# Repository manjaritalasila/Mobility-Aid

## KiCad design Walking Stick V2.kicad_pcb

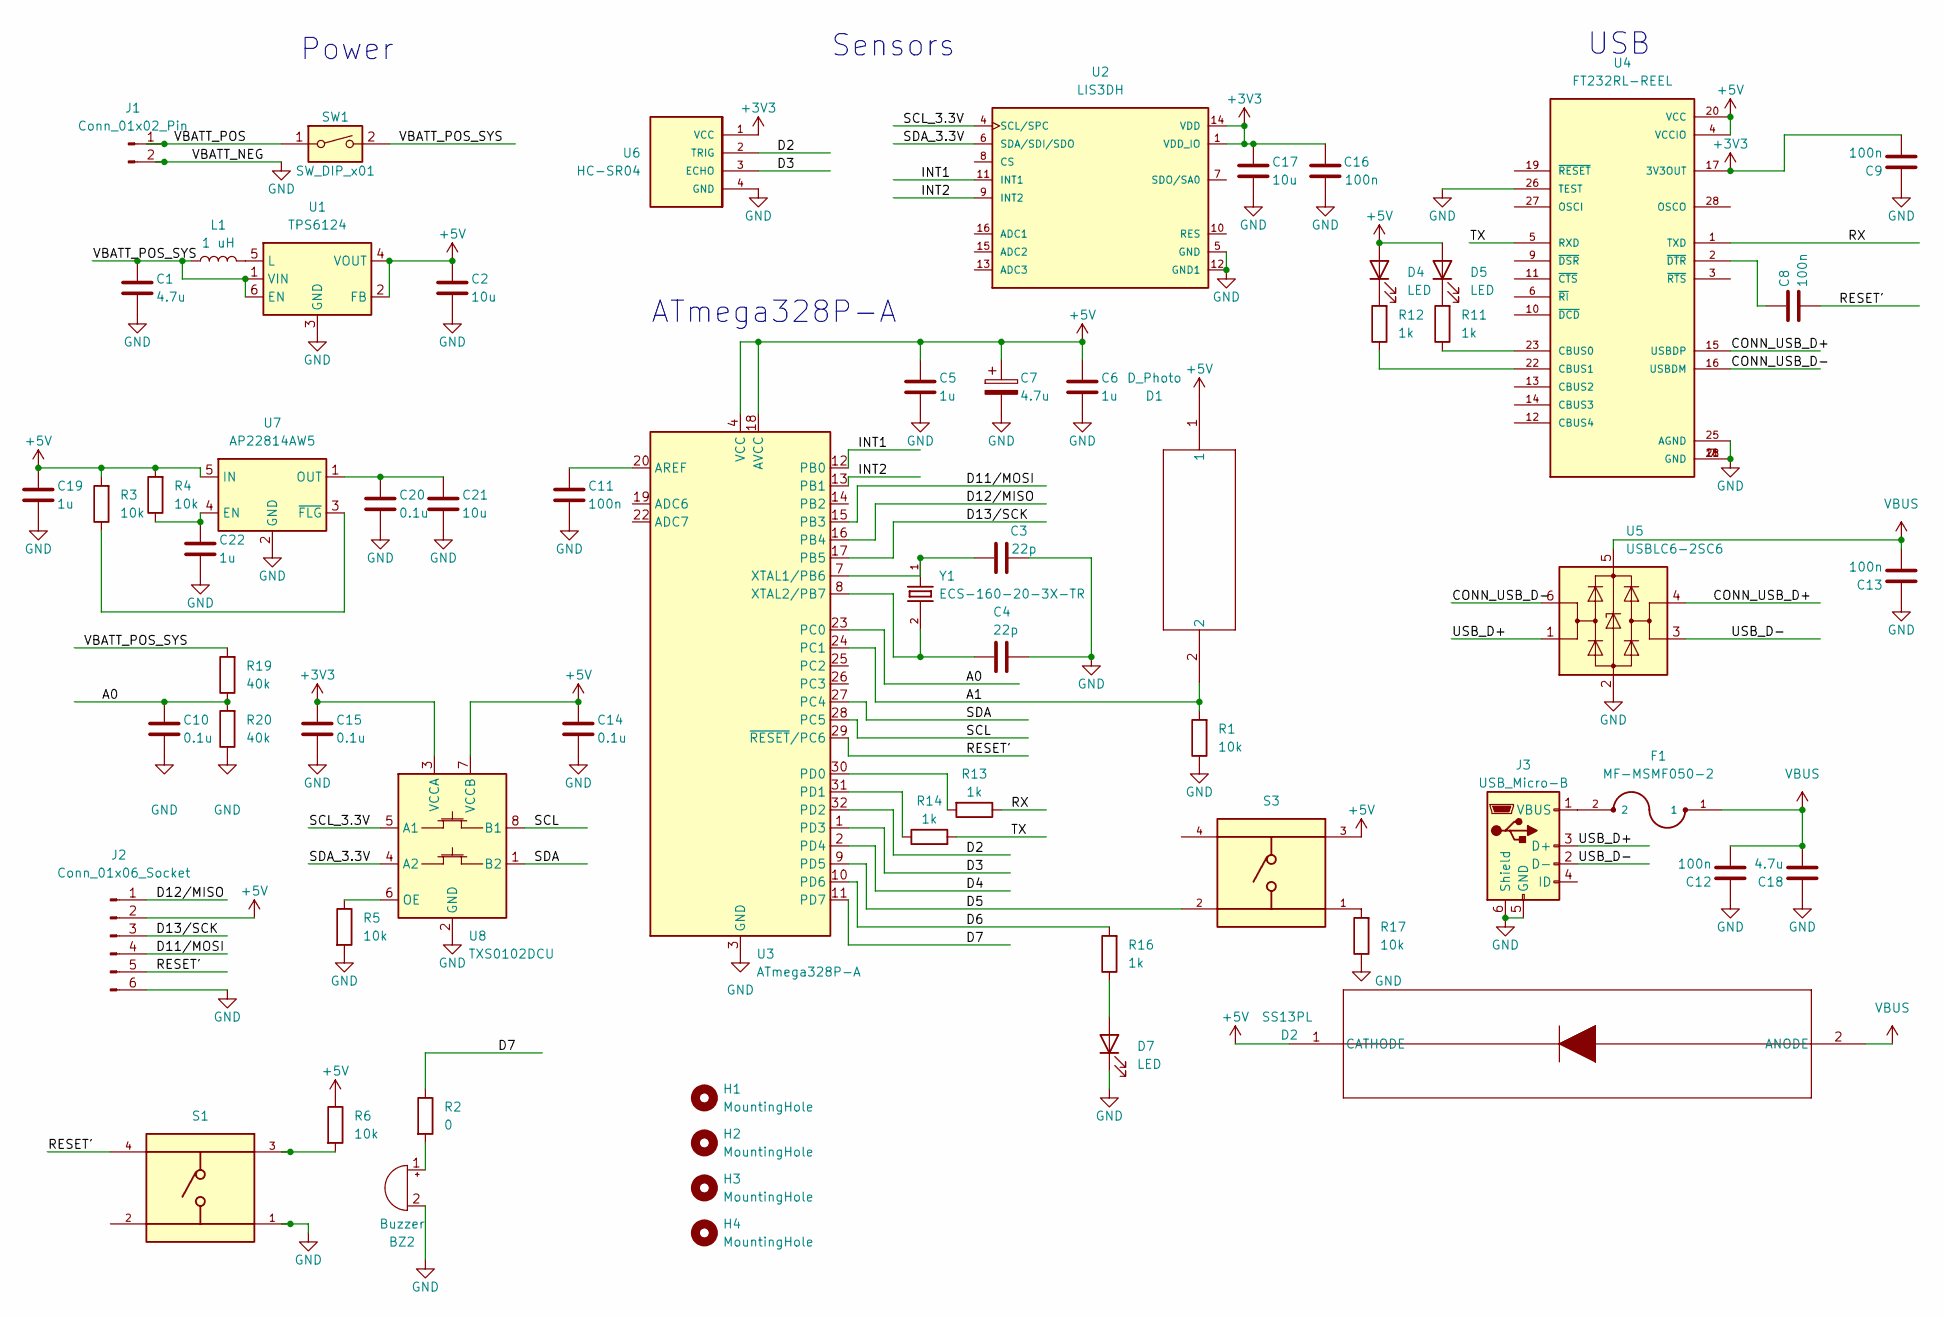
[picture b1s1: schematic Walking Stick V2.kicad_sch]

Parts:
BZ2: Buzzer; Buzzer_12x9.5RM7.6
C1, C7, C18: 4.7u; C_0603_1608Metric
C2, C17, C21: 10u; C_0603_1608Metric
C3, C4: 22p; C_0603_1608Metric
C5, C6, C19, C22: 1u; C_0603_1608Metric
C8, C9, C11, C12, C13, C16: 100n; C_0603_1608Metric
C10, C14, C15, C20: 0.1u; C_0603_1608Metric
D1: D_Photo; TO_NSL_19M_ADP
D2: SS13PL; DIODE_SS1P3L-M3&slash_84A_VIS-L
D4, D5, D7: LED; LED_0402_1005Metric
F1: MF-MSMF050-2; FUSM4632X85
H1, H2, H3, H4: MountingHole; MountingHole_2.1mm
J1: Conn_01x02_Pin; AMASS_XT30UPB-M_1x02_P5.0mm_Vertical
J2: Conn_01x06_Socket; PinHeader_1x06_P2.54mm_Vertical
J3: USB_Micro-B; USB_Micro-B_Molex-105133-0031
L1: 1 uH; L_0603_1608Metric_Pad1.05x0.95mm_HandSolder
R1, R3, R4, R5, R6, R17: 10k; R_0603_1608Metric
R2: 0; R_0603_1608Metric
R11, R12, R13, R14, R16: 1k; R_0603_1608Metric
R19, R20: 40k; R_0603_1608Metric
S1, S3: SW_TS02-66-60-BK-160-LCR-D; PART-NUMBER 471005264152
SW1: SW_DIP_x01; SW_DIP_SPSTx01_Slide_6.7x4.1mm_W6.73mm_P2.54mm_LowProfile_J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
U1: TPS6124; WSON-6-1EP_2x2mm_P0.65mm_EP1x1.6mm
U2: LIS3DH; PQFN50P300X300X100-16N
U3: ATmega328P-A; TQFP-32_7x7mm_P0.8mm
U4: FT232RL-REEL; SOP65P780X200-28N
U5: USBLC6-2SC6; SOT-23-6
U6: HC-SR04; XCVR_HC-SR04
U7: AP22814AW5; SOT-23-5
U8: TXS0102DCU; VSSOP-8_2.3x2mm_P0.5mm
Y1: ECS-160-20-3X-TR; XTAL_ECS-160-20-3X-TR; PARTREV 2017

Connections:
+3V3: C9.2, C15.1, C16.2, C17.1, U2.1 (VDD_IO), U2.14 (VDD), U4.17 (3V3OUT), U6.1 (VCC), U8.3 (VCCA); also elsewhere on the board
+5V: C2.1, C5.1, C6.1, C7.1, C14.1, C19.1, D1.1, D2.1 (CATHODE), D4.2 (A), D5.2 (A), J2.2, R3.2, R4.2, R6.1, S3.3, U1.2 (FB), U1.4 (VOUT), U3.4 (VCC), U3.6 (VCC), U3.18 (AVCC), U4.4 (VCCIO), U4.20 (VCC), U7.5 (IN), U8.7 (VCCB); also elsewhere on the board
/A0: C10.1, R19.1, R20.2, U3.23 (PC0)
/A1: D1.2, R1.2, U3.24 (PC1)
/CONN_USB_D+: U4.15 (USBDP), U5.4 (I/O2)
/CONN_USB_D-: U4.16 (USBDM), U5.6 (I/O1)
/D2: U3.32 (PD2), U6.2 (TRIG)
/D3: U3.1 (PD3), U6.3 (ECHO)
/D4: U3.2 (PD4)
/D5: S3.2, U3.9 (PD5)
/D6: R16.2, U3.10 (PD6)
/D7: R2.1, U3.11 (PD7)
/D11/MOSI: J2.4, U3.15 (PB3)
/D12/MISO: J2.1, U3.16 (PB4)
/D13/SCK: J2.3, U3.17 (PB5)
/INT1: U2.11 (INT1), U3.12 (PB0)
/INT2: U2.9 (INT2), U3.13 (PB1)
/RESET': C8.2, J2.5, S1.4, U3.29 (~RESET/PC6)
/RX: R13.1, U4.1 (TXD)
/SCL: U3.28 (PC5), U8.8 (B1)
/SCL_3.3V: U2.4 (SCL/SPC), U8.5 (A1)
/SDA: U3.27 (PC4), U8.1 (B2)
/SDA_3.3V: U2.6 (SDA/SDI/SDO), U8.4 (A2)
/TX: R14.2, U4.5 (RXD)
/USB_D+: J3.3 (D+), U5.1 (I/O1)
/USB_D-: J3.2 (D-), U5.3 (I/O2)
/VBATT_POS: J1.1, SW1.1
/VBATT_POS_SYS: C1.1, L1.1, R19.2, SW1.2, U1.1 (VIN), U1.6 (EN)
GND: BZ2.2 (+), C1.2, C2.2, C3.2, C4.1, C5.2, C6.2, C7.2, C9.1, C10.2, C11.2, C12.1, C13.1, C14.2, C15.2, C16.1, C17.2, C18.1, C19.2, C20.2, C21.2, C22.2, D7.1 (K), J1.2, J2.6, J3.5 (GND), J3.6 (Shield), R1.1, R5.2, R17.1, R20.1, S1.1, U1.3 (GND), U2.5 (GND), U2.12 (GND1), U3.3 (GND), U3.5 (GND), U3.21 (GND), U4.7 (GND), U4.18 (GND), U4.21 (GND), U4.25 (AGND), U4.26 (TEST), U5.2 (GND), U6.4 (GND), U7.2 (GND), U8.2 (GND); also elsewhere on the board
unnamed: BZ2.1 (-), R2.2
unnamed: D4.1 (K), R12.2
unnamed: D5.1 (K), R11.2
unnamed: D7.2 (A), R16.1
unnamed: F1.2, J3.1 (VBUS)
unnamed: R6.2, S1.3
unnamed: R17.2, S3.1
unnamed: L1.2, U1.5 (L)
unnamed: C11.1, U3.20 (AREF)
unnamed: R13.2, U3.30 (PD0)
unnamed: R14.1, U3.31 (PD1)
unnamed: C3.1, U3.7 (XTAL1/PB6), Y1.1
unnamed: C4.2, U3.8 (XTAL2/PB7), Y1.2
unnamed: R11.1, U4.23 (CBUS0)
unnamed: R12.1, U4.22 (CBUS1)
unnamed: C8.1, U4.2 (~DTR)
unnamed: C22.1, R4.1, U7.4 (EN)
unnamed: C20.1, C21.1, U7.1 (OUT)
unnamed: R3.1, U7.3 (~FLG)
unnamed: R5.1, U8.6 (OE)
VBUS: C12.2, C13.2, C18.2, D2.2 (ANODE), F1.1, U5.5 (VBUS)

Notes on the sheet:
ATmega328P-A
Sensors
Power
USB

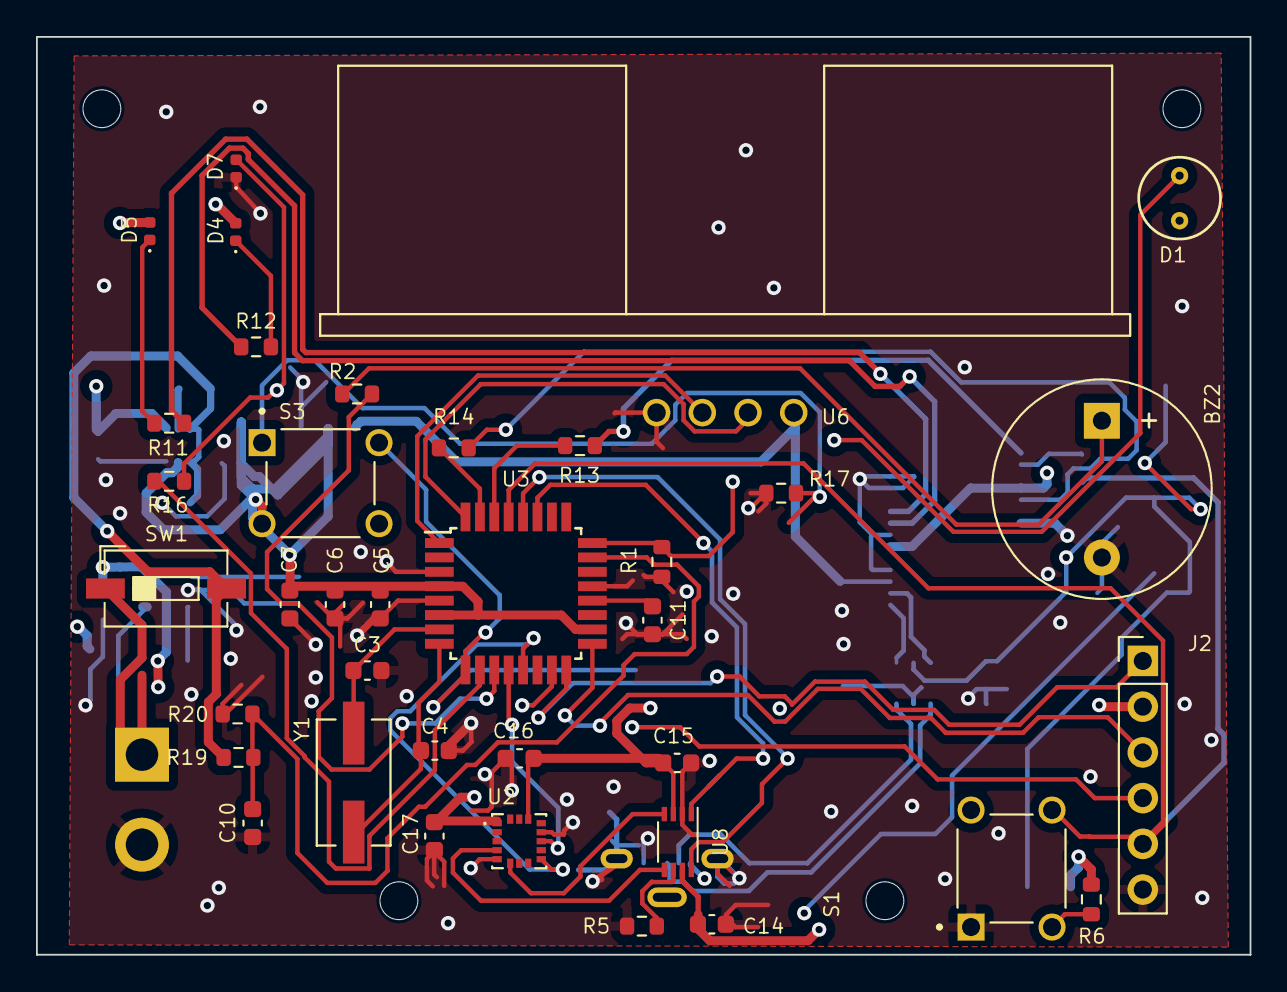
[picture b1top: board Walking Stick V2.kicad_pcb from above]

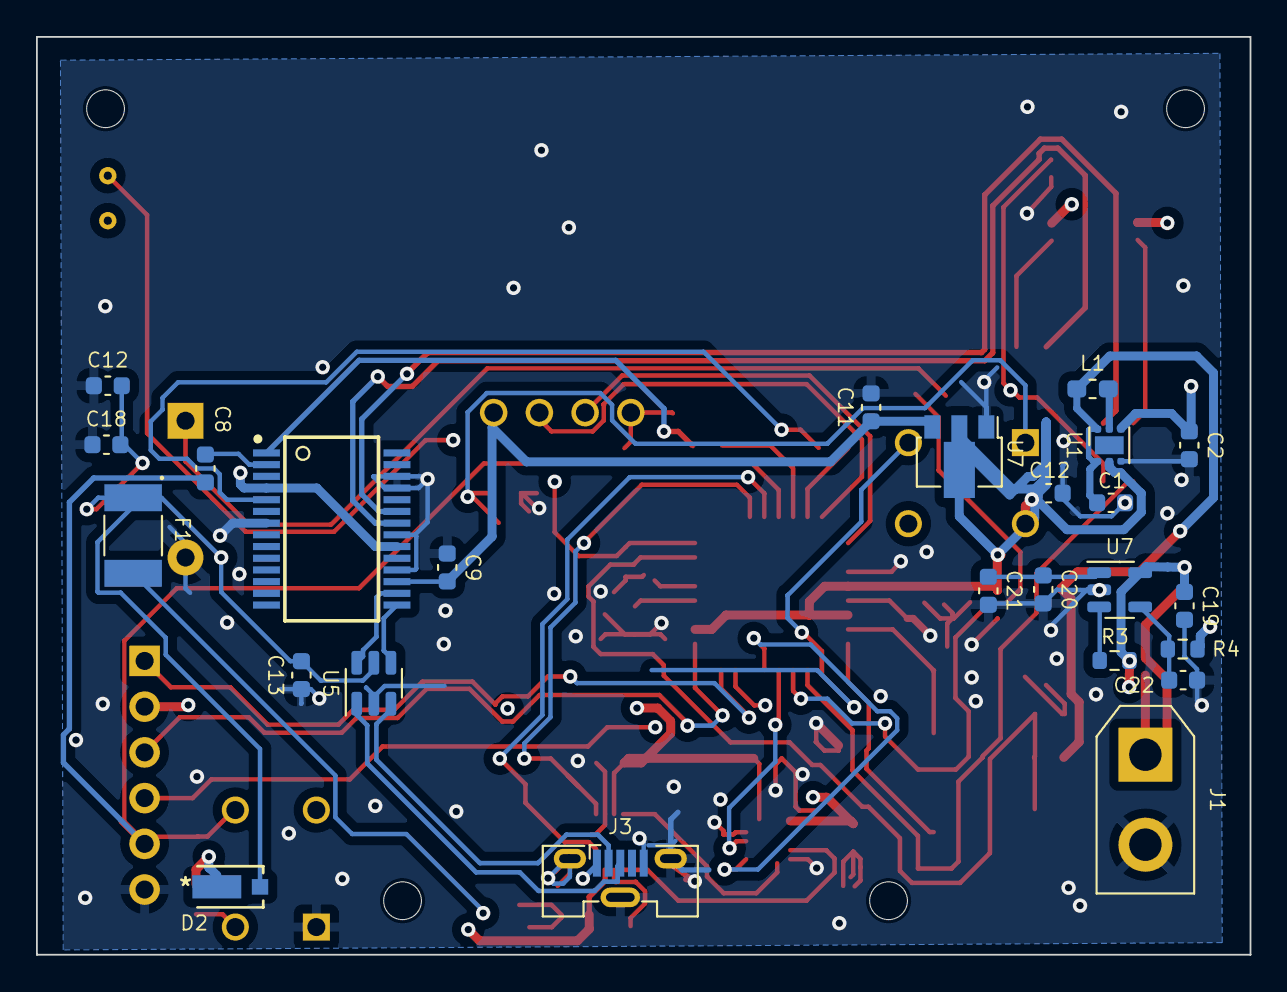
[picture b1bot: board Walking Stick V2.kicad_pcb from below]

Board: 4 copper layers, 67.4 x 51.0 mm, 66 parts (25 on the bottom side), 49 nets.

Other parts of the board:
C11#2, C12#2: 10u; C_0603_1608Metric
U7#2: HT75xx-1-SOT89; SOT-89-3

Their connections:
+3V3: C11#2.1, U7#2.3 (VOUT); also elsewhere on the board
+5V: C12#2.1, U7#2.2 (VIN); also elsewhere on the board
GND: C11#2.2, C12#2.2, U7#2.1 (GND); also elsewhere on the board

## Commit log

2025-01-16 Schematic
